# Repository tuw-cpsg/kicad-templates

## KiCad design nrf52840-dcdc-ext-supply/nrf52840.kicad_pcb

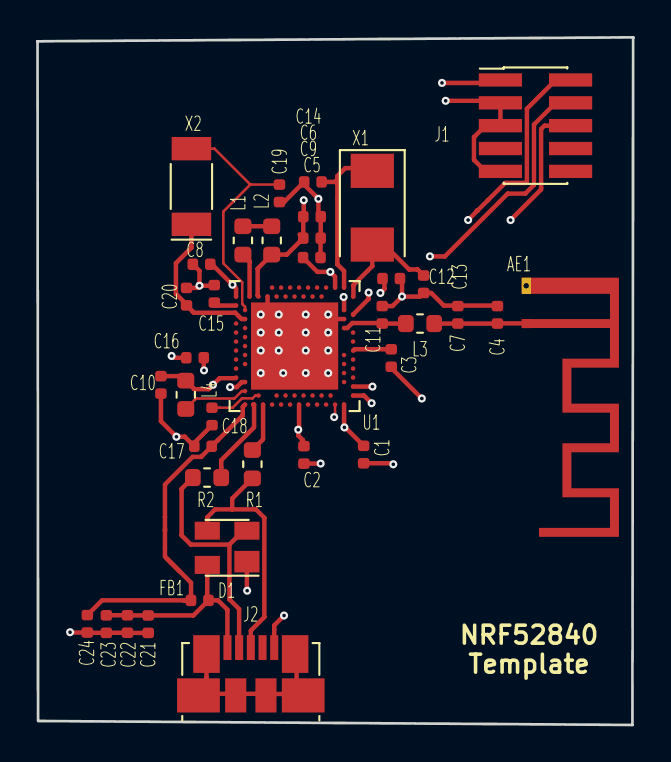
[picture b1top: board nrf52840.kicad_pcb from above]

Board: 4 copper layers, 33.1 x 38.2 mm, 38 parts (0 on the bottom side), 26 nets.

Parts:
AE1: Antenna; Texas_SWRA117D_2.4GHz_Right
C1, C2, C5, C15, C22, C24: 100nF; C_0402_1005Metric
C3: 820pF; C_0402_1005Metric
C4: C; C_0402_1005Metric
C6, C8: 1µF; C_0402_1005Metric
C7, C11: 1pF; C_0402_1005Metric
C9: 47nF; C_0402_1005Metric
C10, C16, C17, C18: 4,7µF; C_0402_1005Metric
C12: 100pF; C_0402_1005Metric
C13, C14, C19, C20: 12pF; C_0402_1005Metric
C21: 10µF; C_0402_1005Metric
C23: 10nF; C_0402_1005Metric
D1: PRTR5V0U2X; SOT-143
FB1: 120R/0,55A; L_0402_1005Metric
J1: Conn_ARM_JTAG_SWD_10; PinHeader_2x05_P1.27mm_Vertical_SMD
J2: USB_B_Micro; USB_Micro-B_Molex_47346-0001
L1: 15nH; L_0603_1608Metric
L2, L4: 10µH; L_0603_1608Metric
L3: 3,9nH; L_0603_1608Metric
R1, R2: 0; R_0603_1608Metric
U1: nRF52840; Nordic_AQFN-73-1EP_7x7mm_P0.5mm
X1: 32MHz; Crystal_SMD_Abracon_ABM3-2Pin_5.0x3.2mm
X2: 32,768kHz; Crystal_SMD_MicroCrystal_CC4V-T1A-2Pin_5.0x1.9mm

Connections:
/ANT: C11.1, L3.2, U1.H23
/D+: R1.1, U1.AD6
/D-: R2.2, U1.AD4
/DCC: L1.1, U1.B3
/DCCH: L4.2, U1.AB2
/DEC1: C15.1, U1.C1
/DEC3: C12.1, U1.D23
/DEC4: C6.1, C9.1, L2.2, U1.B5, U1.E24
/DEC5: C3.1, U1.N24
/DECUSB: C18.1, U1.AC5
/SWDCLK: J1.4, U1.AA24
/SWDIO: J1.2, U1.AC24
/SWO: J1.6, U1.AD22
/XC1: C13.2, U1.B24, X1.2
/XC2: C14.2, U1.A23, X1.1
/XL1: C19.2, U1.D2, X2.2
/XL2: C20.2, U1.F2, X2.1
GND: AE1.2, C1.2, C2.2, C3.2, C4.2, C5.2, C6.2, C7.2, C8.2, C9.2, C10.2, C11.2, C12.2, C13.1, C14.1, C15.2, C16.2, C17.2, C18.2, C19.1, C20.1, C21.2, C22.2, C23.2, C24.2, D1.1, J1.3, J1.5, J1.9, J2.5, U1.B7, U1.EP, U1.F23
LINE: C16.1, U1.Y2
unnamed: AE1.1, C4.1, C7.1, L3.1
unnamed: C21.1, C22.1, C23.1, D1.4, FB1.2, J2.1
unnamed: D1.2, J2.2, R2.1
unnamed: D1.3, J2.3, R1.2
unnamed: L1.2, L2.1
VBUS: C17.1, C24.1, FB1.1, U1.AD2
VCC: C1.1, C2.1, C5.1, C8.1, C10.1, J1.1, L4.1, U1.A22, U1.AD14, U1.AD23, U1.B1, U1.W1

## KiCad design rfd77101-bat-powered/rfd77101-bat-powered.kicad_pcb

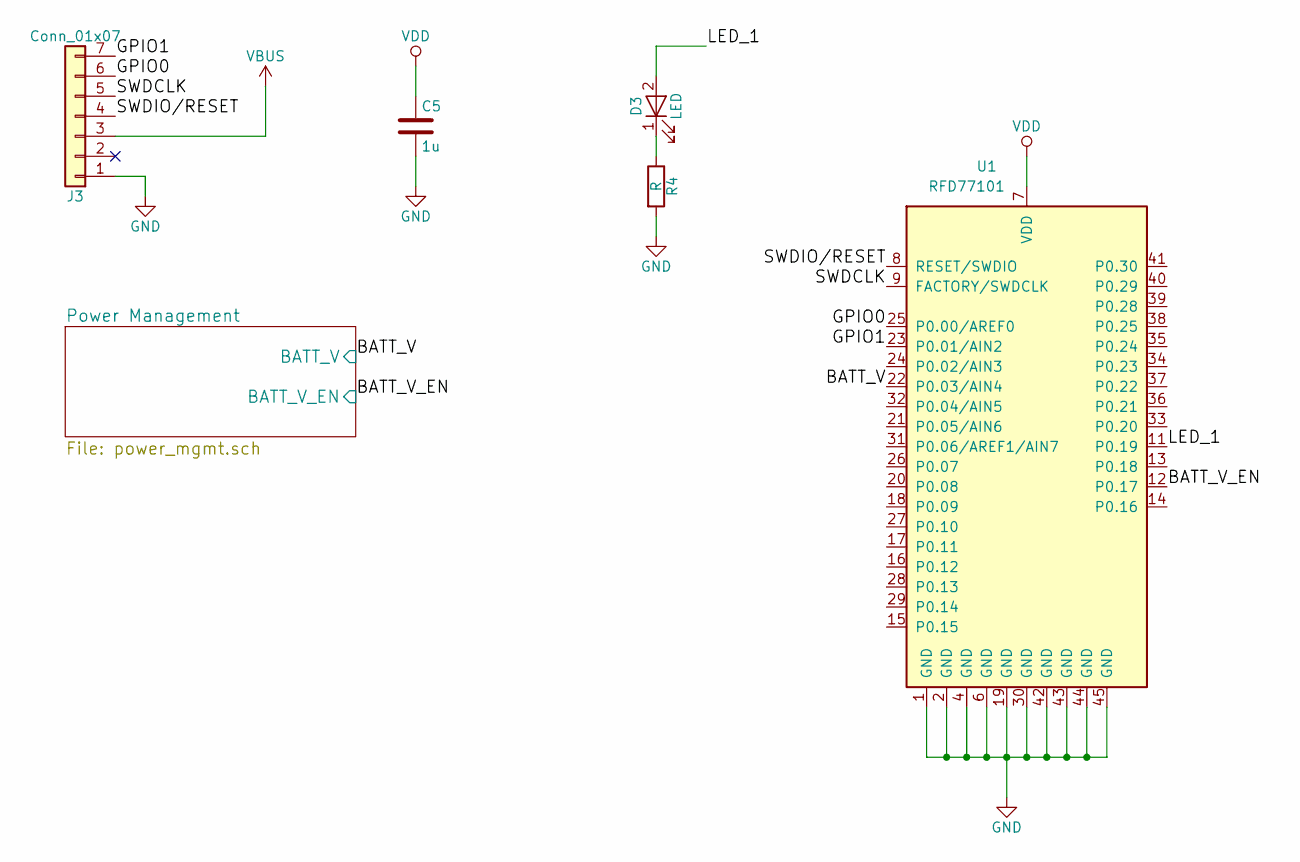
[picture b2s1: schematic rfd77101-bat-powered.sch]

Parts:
C5: 1u; C_0603_1608Metric
D3: LED; LED_0603_1608Metric
J3: Conn_01x07; PinHeader_1x07_P2.54mm_Vertical
R4: R; R_0603_1608Metric
U1: RFD77101; RFDigital_RFD77101

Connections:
/BATT_V: U1.22 (P0.03/AIN4); also elsewhere on the board
/BATT_V_EN: U1.12 (P0.17); also elsewhere on the board
/GPIO0: J3.6, U1.25 (P0.00/AREF0)
/GPIO1: J3.7, U1.23 (P0.01/AIN2)
/LED_1: D3.2 (A), U1.11 (P0.19)
/SWDCLK: J3.5, U1.9 (FACTORY/SWDCLK)
/SWDIO/RESET: J3.4, U1.8 (RESET/SWDIO)
GND: C5.2, J3.1, R4.2, U1.1 (GND), U1.2 (GND), U1.4 (GND), U1.6 (GND), U1.19 (GND), U1.30 (GND), U1.42 (GND), U1.43 (GND), U1.44 (GND), U1.45 (GND); also elsewhere on the board
unnamed: D3.1 (K), R4.1
VBUS: J3.3; also elsewhere on the board
VDD: C5.1, U1.7 (VDD); also elsewhere on the board

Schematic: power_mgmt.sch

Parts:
C1, C2: 4.7u; C_0603_1608Metric
C3, C4: 1u; C_0603_1608Metric
D1, D2: BAT20J; D_SOD-323
J1: USB_OTG; USB_Micro-B_Molex_47346-0001
J2: BATT_CONN; JST_PH_S2B-PH-K_1x02_P2.00mm_Horizontal
Q1: Q_NMOS_GSD; SOT-23
Q2: Q_PMOS_GSD; SOT-23
R1, R5: 1.6k; R_0603_1608Metric
R2: 8.2k; R_0603_1608Metric
R3: 10k; R_0603_1608Metric
U2: MCP73811T-420I-OT; SOT-23-5
U3: TLV74130; SOT-23-5

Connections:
+BATT: C2.1, J2.1, Q2.3, R5.1, U2.3 (VBAT); also elsewhere on the board
/BATT_V: R1.2, R2.1; also elsewhere on the board
/BATT_V_EN: Q1.1; also elsewhere on the board
GND: C1.2, C2.2, C3.2, C4.2, J1.5, J2.2, Q1.2, R2.2, R3.2, U2.2 (VSS), U3.2 (GND); also elsewhere on the board
unnamed: C1.1, D1.2, J1.1, U2.1 (CEN), U2.4 (VDD), U2.5 (PROG)
unnamed: C3.1, D2.1, Q2.2, U3.1 (VIN), U3.3 (EN)
unnamed 13: Q1.3, R5.2; also elsewhere on the board
unnamed 14: R1.1; also elsewhere on the board
VBUS: D1.1, D2.2, Q2.1, R3.1; also elsewhere on the board
VDD: C4.1, U3.5 (VOUT); also elsewhere on the board

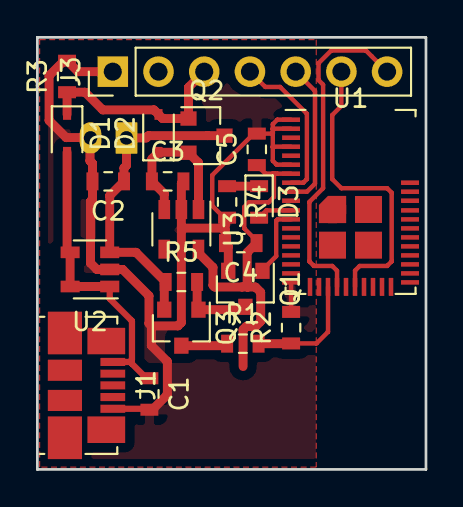
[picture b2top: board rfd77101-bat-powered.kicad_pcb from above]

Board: 2 copper layers, 21.6 x 24.0 mm, 22 parts (1 on the bottom side), 16 nets.

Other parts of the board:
Q3: DMP3099L-13; SOT-23

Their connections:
+BATT: Q3.2; also elsewhere on the board
unnamed 13: Q3.1; also elsewhere on the board
unnamed 14: Q3.3; also elsewhere on the board

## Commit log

2018-02-28 add rfd77101 battery powered template
2018-03-12 update board for better batt measurements
2018-04-09 add meta information
2019-05-15 Added Template for NRF52840 with DCDC ext. supply
2019-06-11 Changed crystal capacitor from 12pF to 18pF.
